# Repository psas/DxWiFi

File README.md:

**NOTE: THIS PROJECT IS DEPRECATED. PLEASE SEE THE OreSat DxWiFi Project for the latest [hardware](https://github.com/oresat/oresat-dxwifi-hardware) and [software](https://github.com/oresat/oresat-dxwifi-software).**

-----

DxWiFi
======

Repo for our Long Distance (also "long range") WiFi testing. The goal is to test out a WiFi-based communication system for amateur rockets, and possibly CubeSats.

Wiki Links on Wireless Configuration
--------

From our PSAS wiki, mostly from the 2005 launch attempt:

- FC WiFi config: <http://psas.pdx.edu/FlightComputerSoftware2002/>
- Link budget: <http://psas.pdx.edu/LinkBudget/>
- Another link budget: <http://psas.github.io/research-notebooks/cubesat-linkbudget/cubesat-linkbudget>
- First discussion with Prof. Jim Binkley: <http://psas.pdx.edu/news/2001-06-27/>
- Second discussion with Prof. Jim Binkley: <http://psas.pdx.edu/news/2004-02-01/>
- Someone thinks madwifi can do ad-hoc demo mode: <http://comments.gmane.org/gmane.linux.kernel.wireless.general/30599>

World Record WiFi Attempts
--------------------------

Obviously, [Wikipedia](http://en.wikipedia.org/wiki/Long-range_Wi-Fi) has an article on long distance WiFi, but it appears to be incorrect (let's fix that after some more digging).

There's a 2002/2003 Guiness Book of World Records entry for long range WiFi of 310 km by the Swedish Space Corporation, at least according to [this press release](http://www.alvarion.com/news-center-sp/global-press-releases/172-guiness-world-records-recognizes-worlds-longest-wi-fi-connection). Wikipedia claims it was 420 km, but that information seems to be wrong.

Going to [GBWR](http://www.guinnessworldrecords.com/) directly, we found that the [current world record is 382 km (237 miles)](http://www.guinnessworldrecords.com/world-records/2000/longest-broadband-wireless-connection), which was set in April 2007 by  Ermanno Pietrosemoli between two mountains in the Venezuelan Andes. He apparently got 3 Mbps, which is pretty good for 382 km!

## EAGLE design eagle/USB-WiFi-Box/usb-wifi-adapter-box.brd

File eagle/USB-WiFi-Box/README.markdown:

# USB WiFi Box

A small breakout board that goes between the
[ZCN-722M](http://www.zcom.com.tw/program1/product_showtext.asp?infoid=C$cE*yQ$x&cmd=1)
WiFi modules and a USB Mini B Connector. The ZCN-722M comes with a 0.1 inch
header with USB pinout. This is brought to a USB Mini B connector for easy
use with a laptop. The stack is then set in a small steel box and RF sealed
with copper tape. This should provide plenty of RF shielding for noise floor
testing.

The Antenna line is broken out from the U.FL connector on the board to an SMA
on the side of the box via a short cable.

## Boards

Layout:

Finished and stuffed in boxes:

# Buildlog

### Dec 25, 2013

Completed breakout boards and one box.

### Dec 30, 2013

Finished other box, both WiFi Modules ready to go.

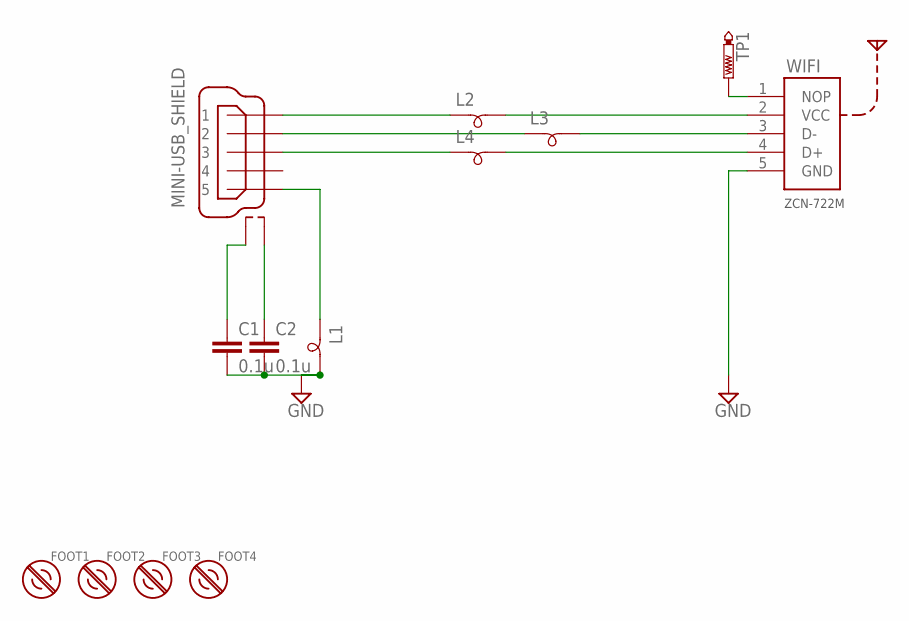
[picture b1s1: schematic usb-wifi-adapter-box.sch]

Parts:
C1, C2: 0.1u; C0805
CONN1: MINI-USB_SHIELD; RUGGEDUSB
FOOT1, FOOT2, FOOT3, FOOT4: _4-BARE_MOUNTING_HOLE/.400; _4/.400-BARE+STD_TOOL_CLEARANCE
L1, L2, L3, L4: INDUCTOR-BEAD; R0805
TP1: PTR1PAD1-13; P1-13
WIFI: ZCN-722M

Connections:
D+: L4.2, WIFI.4 (D+)
D+OUT: CONN1.3, L4.1
D-: L3.2, WIFI.3 (D-)
D-OUT: CONN1.2, L3.1
GND: C1.2, C2.2, L1.2, WIFI.5 (GND)
GNDOUT: CONN1.5, L1.1
unnamed: TP1.TP, WIFI.1 (NOP)
SHEILDGND1: C2.1, CONN1.SHLD@2 (S2)
SHIELDGND2: C1.1, CONN1.SHLD@1 (S1)
VCC: L2.2, WIFI.2 (VCC)
VCC_OUT: CONN1.1, L2.1

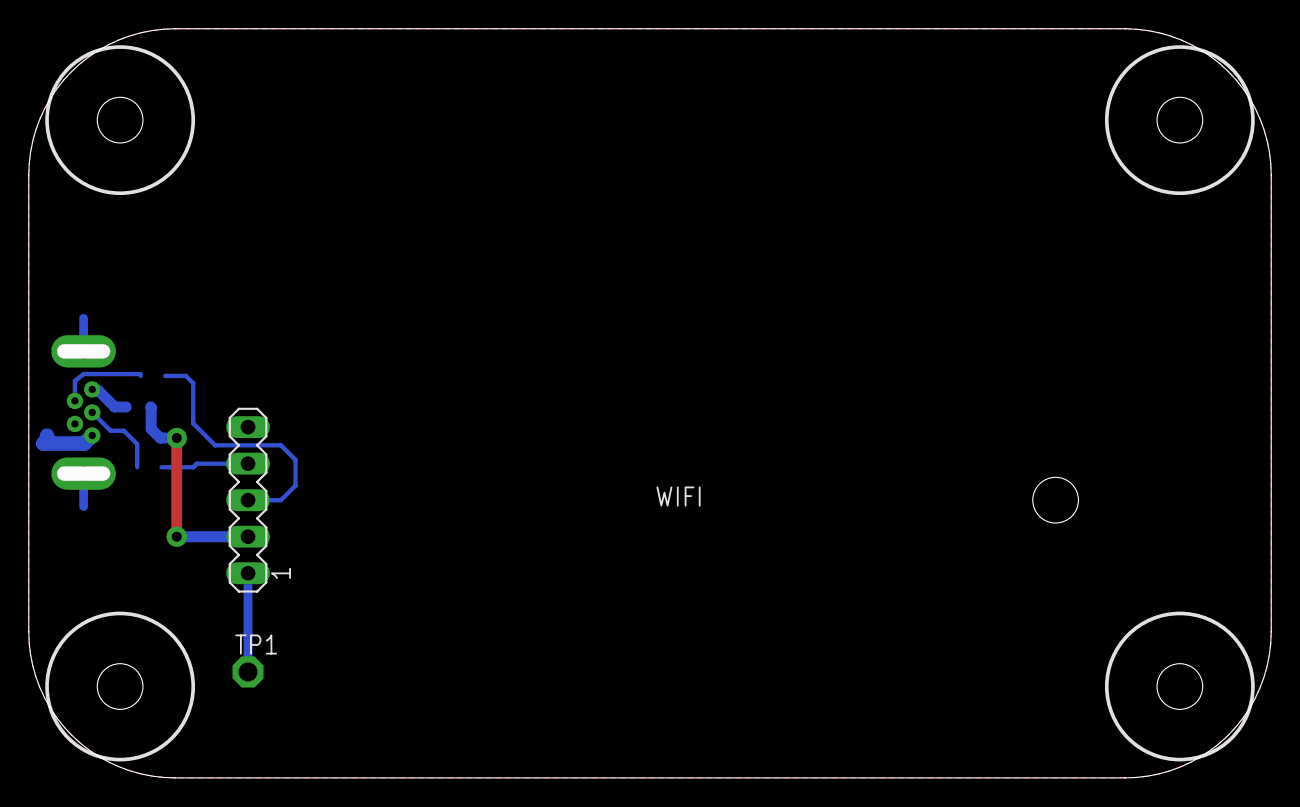
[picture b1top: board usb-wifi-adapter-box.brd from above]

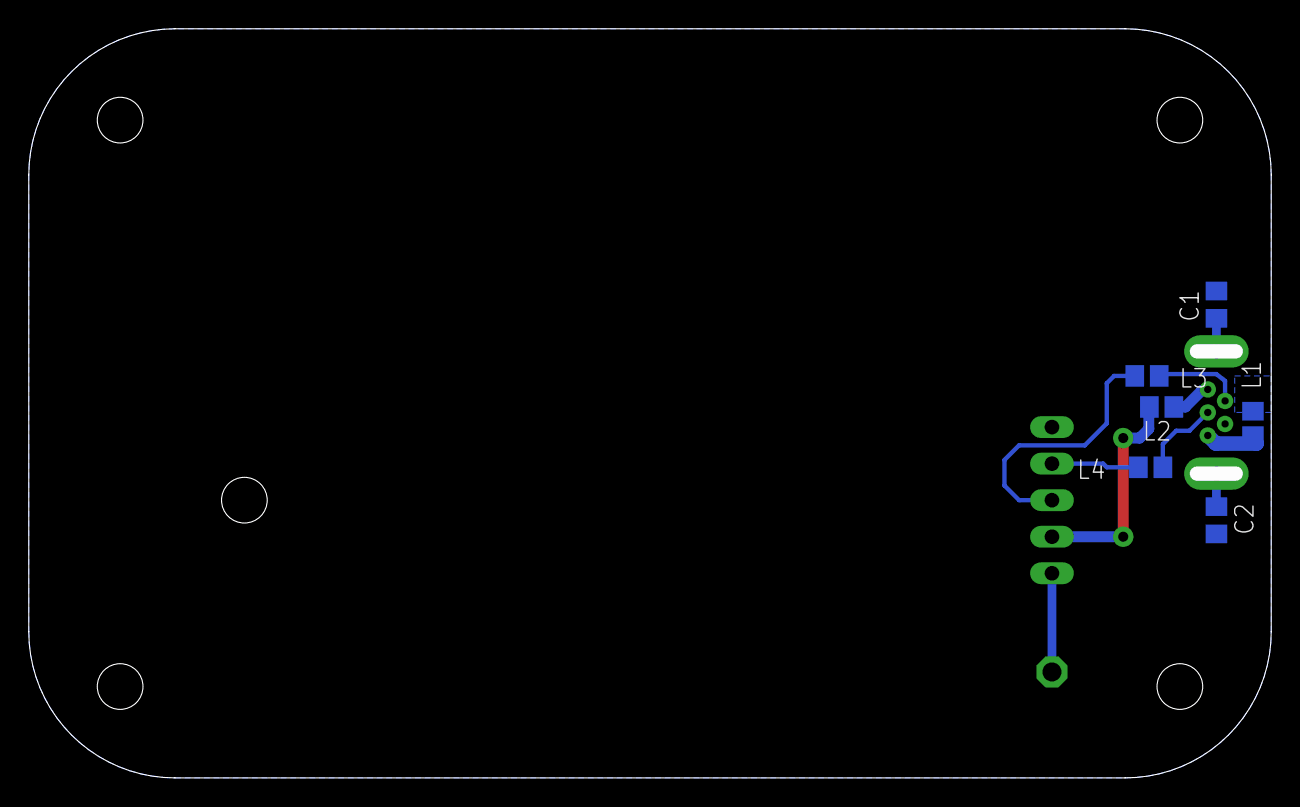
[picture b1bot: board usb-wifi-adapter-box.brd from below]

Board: 2 copper layers, 85.4 x 51.1 mm, 13 parts (6 on the bottom side), 11 nets.

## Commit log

2013-11-14 Project Proposal & Link Budget
2013-11-14 Update README.md
    Added link to ipython notebook link budget from 2013
2013-11-14 Slant Range Calculations
2013-11-16 Changed numbers to something a bit more reasonable.
2013-12-02 Changed values for 500 km and a 20 dB dish.
2013-12-21 starting eagle files for USB WiFi adapter that sits in an altoids tin
2013-12-21 inductors and shild ground caps
2013-12-23 mounting holes in schematic and placeholder starter for wifi header
2013-12-23 Measured USB board, finished schematic
2013-12-24 layout altoid box and drop all the parts
2013-12-24 board layout v1, using one wire for VCC, fixed slots in USB part
2013-12-24 fix routing issues
2013-12-30 minor fixes, values of caps
2013-12-30 readme and pictures for the wifi box
2014-01-12 Reformatted and simplified link budget calcs, and added latest numbers from DxWiFi test.
2014-01-14 Checked in initial version of wifi configuration script
2014-01-14 moving automation to a project in this repo
2014-01-15 very early version (not tested) of python automation
2014-01-15 Converted shell script to pythong (untested)
2014-01-20 config parser
2014-01-20 automation is a work in progress
2014-01-21 cat file path befor subprocess call
2014-01-21 test of Popen vs call
2014-01-21 Working on issue with calls to ifconfig hanging
2014-01-22 bug fixes for test-wifi
2014-01-22 config fix
2014-01-22 test click corruption
2014-01-22 working version of test-wifi
2014-01-22 fixed directory creation bug
2014-01-22 removed dumpfile truncation
2014-01-22 fixed test-wifi timing and added temporary click file
2014-01-22 added .dist suffix to click test file
2014-01-22 added test.click.dist -needs to be appropriately commented
2014-01-22 wrote signal strength finder
2014-01-22 added .click file that sends infinite packets
2014-01-25 Sending tcpdump a signal that will cause it to write out packets before exiting
2014-01-25 added debug prints
2014-01-25 single bit change
2014-01-25 added logs folder and 1st logs
2014-01-25 added 2nd close range tests
2014-01-25 made names make sense
2014-01-26 slight modification to sourcefinder
2014-01-26 added logs from today's dx test
2014-01-26 Logs from rocky butte side of dx test
2014-01-26 Outline of field test notes.
2014-01-26 reformat fieldtest notes
2014-01-27 added photos to test writeup
2014-01-27 readme
2014-01-27 add team photo at RB
2014-01-27 missed dot in filename
2014-01-27 Added Council Crest photos
2014-01-27 markdown won't follow links.
2014-01-27 Rotate two photos to proper orientation...
2014-01-29 packet building script
2014-01-29 allowed broadcast
2014-01-29 added gps-source file
2014-01-29 GPS can drop and reconnect without breaking everything
2014-01-31 changes to rate algorithm, and minor packet realignment
2014-01-31 added quick and dirty gps tester
2014-01-31 made sleeptime between packets negative safe (can be slower than it should for rate for small packets)
2014-02-02 data parser for pcap files
2014-02-02 rate.pcap removed
2014-02-02 removed rate.pcap
2014-02-02 fake data for parsing
2014-02-02 pushing plane dump files before arranging them to ensure I don't accidentally delete them all
2014-02-02 placed pcap files in plane-test dir
2014-02-02 working gparse
2014-02-03 Update README.markdown
    Link to new field test day
2014-02-03 renamed pcap files from flight test to make chronology more apparent
2014-02-03 Cleaned up test notes. Added on for today's test, to be added.
2014-02-03 Moved to data to the right place
2014-02-03 Added GPS coordinate
2014-02-03 gparse working with gdocs... almost
2014-02-03 Renamed single digit capture files for sorting
2014-02-03 These pcap log parsers will help with pulling out GPS data. Hackish and ugly. Please delete before and/or after replacing them with something better.
2014-02-03 Added a slightly more useful script purpose comment.
2014-02-03 Photos from yesterday's field test, plus an updated link budget.
2014-02-03 GBWR != Great Britain Wheelchair Rugby
    At least, not in this context.
2014-02-04 Added some results from parsing through logs
2014-02-05 parses gps data to DDD
2014-02-05 gps data in csv and deduplicated, DDD format csv.
2014-02-06 Added some ground pictures from Glenn
2014-02-06 fix image links
2014-02-07 updated test details for 2014-01-26-1130-patch_to_helical
2014-02-09 Added flight test photos from the plane.
2014-02-09 Updated writeup to include photos and post link.
2017-12-02 Create README.md
    Created a place for these test notes
2017-12-02 Add files via upload
    Photos of 10-Jan-2014 Atheros link test in EB garage
2017-12-02 Create 2014-01-10-fieldtest_eb_garage.mdwn
    Test notes for 12 meter DxWiFi test
2017-12-02 Update 2014-01-10-fieldtest_eb_garage.mdwn
    Putting together testing notes
2017-12-02 Create 2014-01-10-photos
2017-12-02 Add files via upload
    Reload files with acceptable file names. Sheesh!
2019-02-11 Point to the latest DxWiFi project.
